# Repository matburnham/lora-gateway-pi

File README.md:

# Raspberry Pi LoRa gateway HAT for RFM9x, DRF1278F and XL1278-SMT boards

A somewhat 'universal' LoRa gateway HAT for RFM9x, DRF1278F and XL1278-SMT boards loosely based upon [Raspberry Pi+ LoRa(TM) Expansion Board](https://store.uputronics.com/index.php?route=product/product&path=61&product_id=68) and designed for the [PiInTheSky/lora-gateway](https://github.com/PiInTheSky/lora-gateway) code.

_Populated module installed on a Rapsberry Pi 2_

# Configuration

The board is designed for use with [PiInTheSky/lora-gateway](https://github.com/PiInTheSky/lora-gateway). See [Software/gateway-sample.txt](Software/gateway-sample.txt) for a starting point configuration. Note DIO5_0=1 must be set as unlike the rest it is not the default. WiringPi seems to rather unhelpfully offer a third 'standard' for Rapsberry Pi pins. [WiringPi GPIO pinout](https://pinout.xyz/pinout/wiringpi_gpio_pinout) is good reference showing equivalent BCM, WiringPi and expansion header pin numbers.

# Testing

Only the configuration pictured above (DRF1278F in CE0 and XL1278-SMT in CE1) has been tested. Neither the indicator LEDs nor the Pi hat EEPROM have been populated and tested yet.

Note [PCB layout issues with v1.0](https://github.com/matburnham/lora-gateway-pi/issues/1), notably that the XL1278-SMT footprint is slightly out as the through-holes don't line up. Surface mounting the module works perfectly fine.

# Module identification

_HOPERF RFM98W_

_Dorji DRF1287F_

_HR-WT XL1278-SMT_

Note: while the DRF1278F and XL1278-SMT boards look similar, their pinouts are significantly different.

## Confusion

There is a lot of confusion between Ebay and AliExpress sellers alike. One ebay seller even showing photos of both types of boards on the same listing. So check carefully, or use what you're given with this either/or breakout.

# Documentation

CI/CD documentation generation 

TODO: links to generated documentation, etc.

## Version 1.0

## Version 1.1

# Libraries

* KiCad symbol and footprint libraries for DRF1278F and XL1278-SMT for KiCad are at [kicad-libs](https://github.com/matburnham/kicad-libs)

# References

* Inspired by Uputronics' [Raspberry Pi+ LoRa(TM) Expansion Board](https://store.uputronics.com/index.php?route=product/product&path=61&product_id=68)

* [Dorji DRF1278F datasheet](http://www.dorji.com/docs/data/DRF1278F.pdf) | [respository copy](Docs/DRF1278F.pdf)
* Closest information to a [XL1278-SMT datasheet](http://www.hr-wt.com/html_products/XL1278-SMT-59.html) | [respository screenshot](Docs/screencapture-hr-wt-html-products-XL1278-SMT-59-html-2021-02-26-15_49_33.png)

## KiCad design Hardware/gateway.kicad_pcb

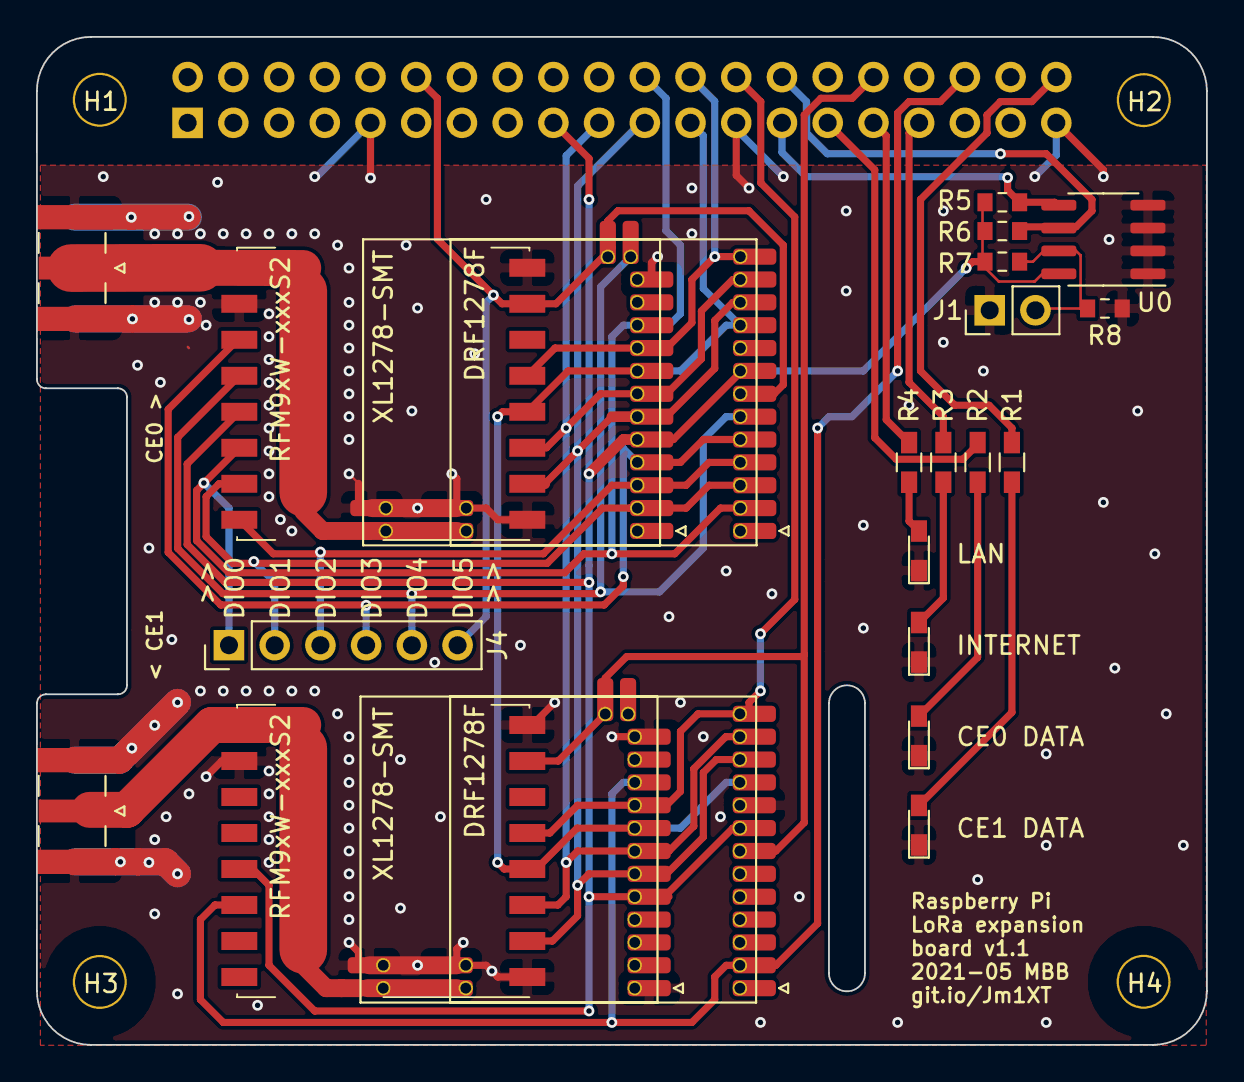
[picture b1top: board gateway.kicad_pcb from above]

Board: 2 copper layers, 65.0 x 56.0 mm, 28 parts (1 on the bottom side), 28 nets.

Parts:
D1, D2, D3, D4: LED; LED_0603_HandSoldering
H1, H2, H3, H4: 3mm_Mounting_Hole; NPTH_3mm_ID
J0: Raspberry_Pi_2_3_40HAT; PinSocket_2x20_P2.54mm_Vertical
J1: CONN_01X02; PinHeader_1x02_P2.54mm_Vertical
J2, J3: Conn_Coaxial; SMA_Samtec_SMA-J-P-X-ST-EM1_EdgeMount
J4: Conn_01x06; PinHeader_1x06_P2.54mm_Vertical
R1, R2, R3, R4: 330; R_0603_HandSoldering
R5, R6: 3.9K; R_0603_1608Metric_Pad0.84x1.00mm_HandSolder
R7: 10K; R_0603_1608Metric_Pad0.84x1.00mm_HandSolder
R8: DNP; R_0603_1608Metric_Pad0.84x1.00mm_HandSolder
U0: CAT24C32; SOIC-8_3.9x4.9mm_P1.27mm
U0a1, U1a1: DRF1278F
U0b1, U1b1: XL1278-SMT
U0c1, U1c1: RFM9xW-xxxS2; Hopref_RFM9XW_SMD

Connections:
0_ANT: J2.1, U0a1.15, U0b1.16, U0c1.9
0_DATA_LED: J0.29, R2.1
0_DIO0: J0.22, J4.1, U0a1.2, U0b1.10, U0c1.14
0_DIO1: J4.2, U0a1.3, U0b1.2, U0c1.15
0_DIO2: J4.3, U0a1.4, U0b1.3, U0c1.16
0_DIO3: J4.4, U0a1.5, U0b1.4, U0c1.11
0_DIO4: J4.5, U0a1.6, U0b1.13, U0c1.12
0_DIO5: J0.12, J4.6, U0a1.7, U0b1.14, U0c1.7
0_NSS: J0.24, U0a1.13, U0b1.9, U0c1.5
1_ANT: J3.1, U1a1.15, U1b1.16, U1c1.9
1_DATA_LED: J0.40, R1.1
1_DIO0: J0.36, U1a1.2, U1b1.10, U1c1.14
1_DIO5: J0.32, U1a1.7, U1b1.14, U1c1.7
1_NSS: J0.26, U1a1.13, U1b1.9, U1c1.5
/ID_SC_EEPROM: J0.28, R6.2, U0.6
/ID_SD_EEPROM: J0.27, R5.2, U0.5
GND: D1.1, D2.1, D3.1, D4.1, J0.9, J0.25, J0.39, J1.1, J2.2, J3.2, R8.2, U0.1, U0.2, U0.3, U0.4, U0a1.9, U0a1.14, U0b1.1, U0b1.12, U0b1.15, U0c1.1, U0c1.8, U0c1.10, U1a1.9, U1a1.14, U1b1.1, U1b1.12, U1b1.15, U1c1.1, U1c1.8, U1c1.10
INTERNET: J0.33, R3.1
LAN: J0.31, R4.1
MISO: J0.21, U0a1.11, U0b1.6, U0c1.2, U1a1.11, U1b1.6, U1c1.2
MOSI: J0.19, U0a1.12, U0b1.7, U0c1.3, U1a1.12, U1b1.7, U1c1.3
unnamed: D1.2, R1.2
unnamed: D2.2, R2.2
unnamed: D3.2, R3.2
unnamed: D4.2, R4.2
unnamed: J1.2, R7.2, R8.1, U0.7
SCK: J0.23, U0a1.10, U0b1.8, U0c1.4, U1a1.10, U1b1.8, U1c1.4
VCC: J0.17, R5.1, R6.1, R7.1, U0.8, U0a1.8, U0b1.5, U0c1.13, U1a1.8, U1b1.5, U1c1.13

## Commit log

2021-03-01 Initial import of handiwork.
2021-03-01 Fix antenna ground connections
2021-03-01 Fix more grounds.
2021-03-01 Final fix.
2021-03-19 Crop rendered images.
2021-03-19 Add missing images.
2021-03-19 Image of actual board.
2021-03-20 Sample config file.
2021-03-20 Populated board
2021-05-11 Adjust footprints and add vias as per #1 Updated XL1278-SMT and DRF1278F footprints from matburnham/kicad-libs#1. Changed SMA footprint. Added some more GND vias.
2021-05-13 Tweaks for #1.
2021-05-13 Fix #2 Adds a breakout for CE0, but not for CE1 as there's insufficient space.
2021-05-13 Renders for v1.1
2021-05-13 Update README.md
    Add renders of v1.1
